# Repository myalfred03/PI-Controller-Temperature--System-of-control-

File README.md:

# PI-Controller-Temperature--System-of-control-
Design control PI  for  Boiler as plant

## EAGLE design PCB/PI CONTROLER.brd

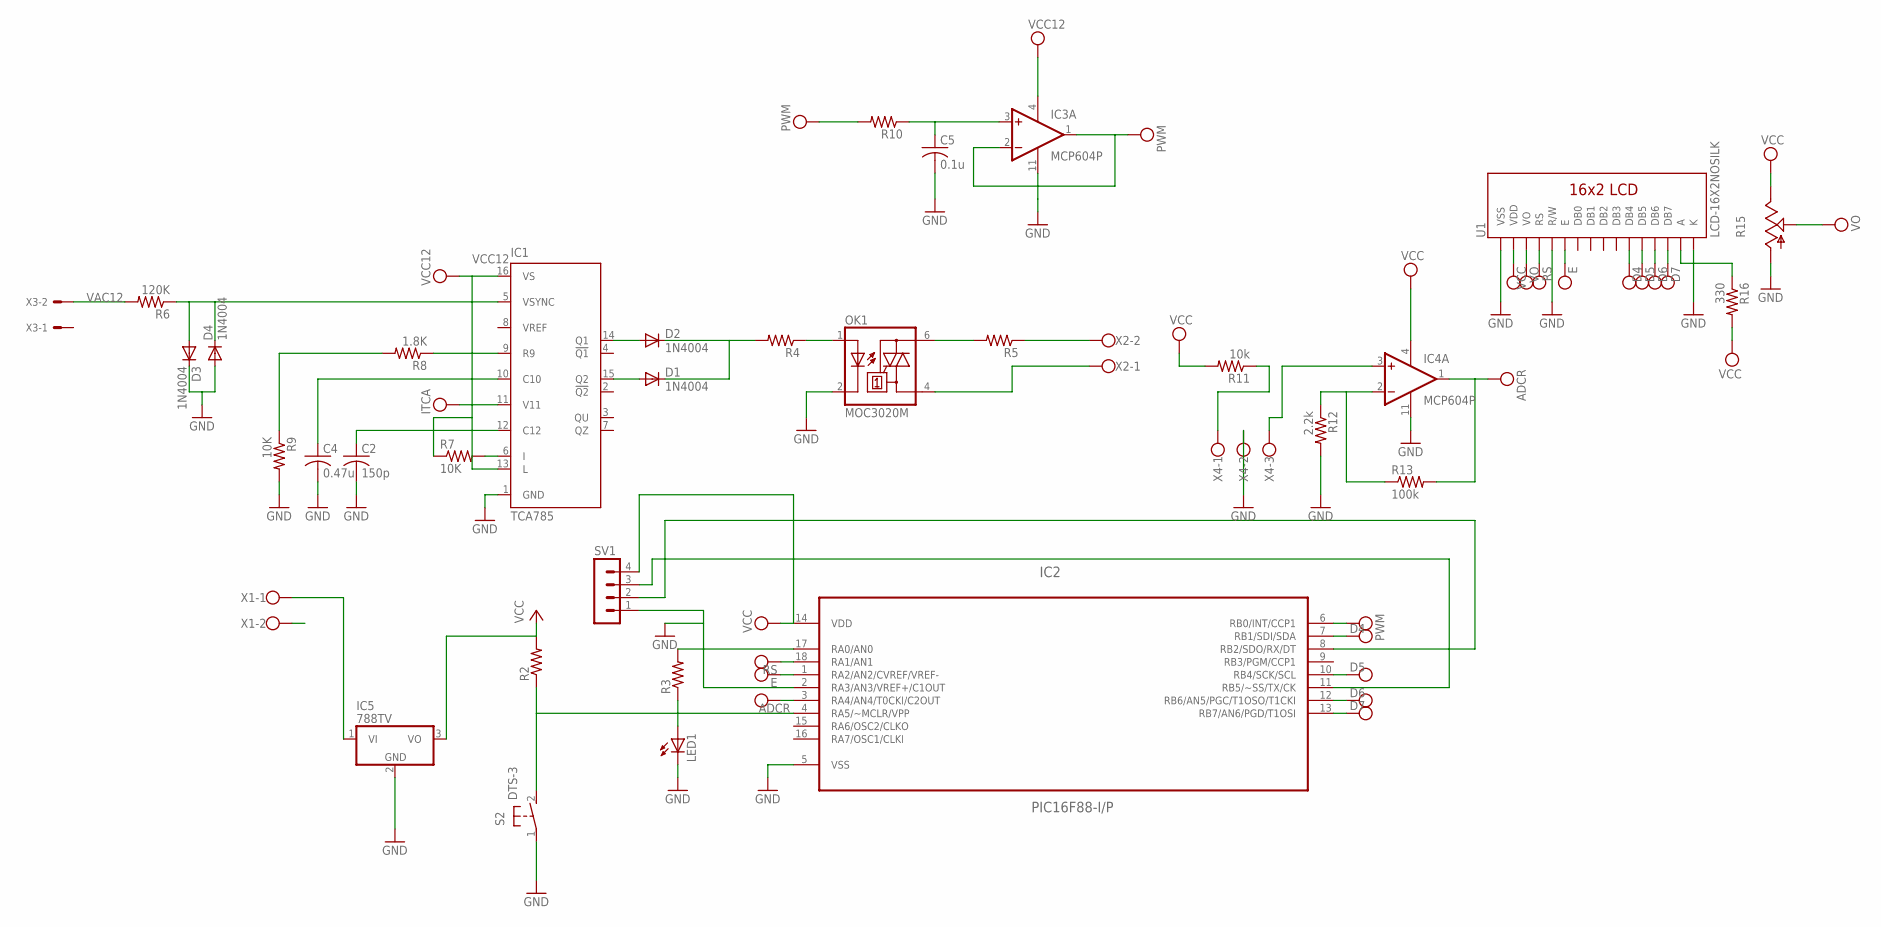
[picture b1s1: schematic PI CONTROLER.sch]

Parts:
C2: 150p; C025-025X050
C4: 0.47u; C050-025X075
C5: 0.1u; C050-025X075
D1, D2, D3, D4: 1N4004; DO41-10
IC1: TCA785; DIL16
IC2: PIC16F88-I/P; DIP254P762X432-18
IC3, IC4: MCP604P; DIL14
IC5: 788TV; TO220V
LED1: LED5MM
OK1: MOC3020M; DIL06
R2, R3, R4, R5, R10: R-US_0207/10; 0207/10
R6: 120K; 0207/10
R7, R9: 10K; 0207/10
R8: 1.8K; 0207/10
R11: 10k; 0207/10
R12: 2.2k; 0207/10
R13: 100k; 0207/10
R15: TRIM_US-RS3; RS3
R16: 330; 0207/10
S2: DTS-3
SV1: MA04-1
U1: LCD-16X2NOSILK; LCD-16X2_NOSILK
X1, X2: W237-102
X3: KK-156-2
X4: W237-103

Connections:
ADCR: IC2.3 (RA4/AN4/T0CKI/C2OUT), IC4.1 (OUT), R13.2
D4: IC2.7 (RB1/SDI/SDA), U1.11 (DB4)
D5: IC2.10 (RB4/SCK/SCL), U1.12 (DB5)
D6: IC2.12 (RB6/AN5/PGC/T1OSO/T1CKI), U1.13 (DB6)
D7: IC2.13 (RB7/AN6/PGD/T1OSI), U1.14 (DB7)
E: IC2.1 (RA2/AN2/CVREF/VREF-), U1.6 (E)
GND: C2.2, C4.2, C5.2, D3.C, D4.A, IC1.1 (GND), IC2.2 (RA3/AN3/VREF+/C1OUT), IC2.5 (VSS), IC3.11 (V-), IC4.11 (V-), IC5.2 (GND), LED1.K (C), OK1.2 (C), R9.2, R12.2, R15.A, S2.1, SV1.1, U1.1 (VSS), U1.5 (R/W), U1.16 (K), X1.2, X4.2
ITCA: IC1.11 (V11), IC3.1 (OUT), IC3.2 (-IN)
unnamed: IC2.4 (RA5/~MCLR/VPP), R2.1, S2.2
unnamed: IC2.17 (RA0/AN0), R3.2
unnamed: C2.1, IC1.12 (C12)
unnamed: IC2.11 (RB5/~SS/TX/CK), SV1.3
unnamed: C4.1, IC1.10 (C10)
unnamed: D2.A, IC1.14 (Q1)
unnamed: LED1.A, R3.1
unnamed: R5.1, X2.2
unnamed: D1.A, IC1.15 (Q2)
unnamed: D1.C, D2.C, R4.2
unnamed: OK1.1 (A), R4.1
unnamed: OK1.6 (A2), R5.2
unnamed: OK1.4 (A1), X2.1
unnamed: D3.A, D4.C, IC1.5 (VSYNC), R6.1
unnamed: IC1.6 (I), R7.2
unnamed: IC1.9 (R9), R8.1
unnamed: R8.2, R9.1
unnamed: C5.1, IC3.3 (+IN), R10.1
unnamed: R11.1, X4.1
unnamed: IC4.3 (+IN), X4.3
unnamed: IC4.2 (-IN), R12.1, R13.1
unnamed: R16.1, U1.15 (A)
unnamed: IC2.8 (RB2/SDO/RX/DT), SV1.2
PWM: IC2.6 (RB0/INT/CCP1), R10.2
RS: IC2.18 (RA1/AN1), U1.4 (RS)
VAC12: R6.2, X3.2
VCC: IC2.14 (VDD), IC4.4 (V+), IC5.3 (VO), R2.2, R11.2, R15.E, R16.2, SV1.4, U1.2 (VDD)
VCC12: IC1.13 (L), IC1.16 (VS), IC3.4 (V+), IC5.1 (VI), R7.1, X1.1
VO: R15.S, U1.3 (VO)

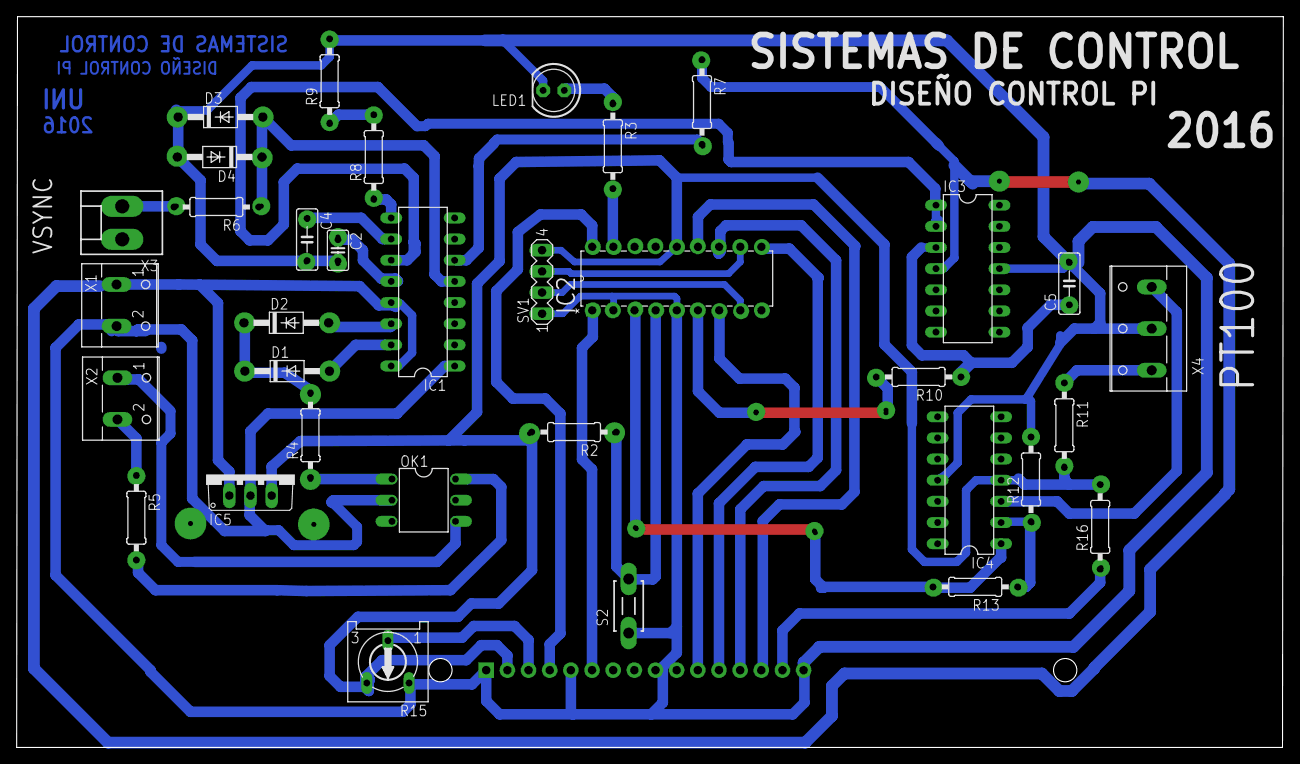
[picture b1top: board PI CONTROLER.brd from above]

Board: 2 copper layers, 152.1 x 87.7 mm, 35 parts (0 on the bottom side), 37 nets.

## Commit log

2016-11-17 :neckbeard: Added .gitattributes & .gitignore files
2016-11-17 Revert ":neckbeard: Added .gitattributes & .gitignore files"
    This reverts commit 9b13a6ba5b7a5ebb416c37701f00dfad03ad8794.
2016-11-17 Programation and simulation
    System of control
2016-11-17 l
    j
2016-12-30 Final PIC16F14459 with OSC EXT
    Final Project Temperature
2017-01-20 PCB PID

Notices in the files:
parts and their libraries:
SparkFun-Displays: Licensing: Creative Commons ShareAlike 4.0 International - https://creativecommons.org/licenses/by-sa/4.0
